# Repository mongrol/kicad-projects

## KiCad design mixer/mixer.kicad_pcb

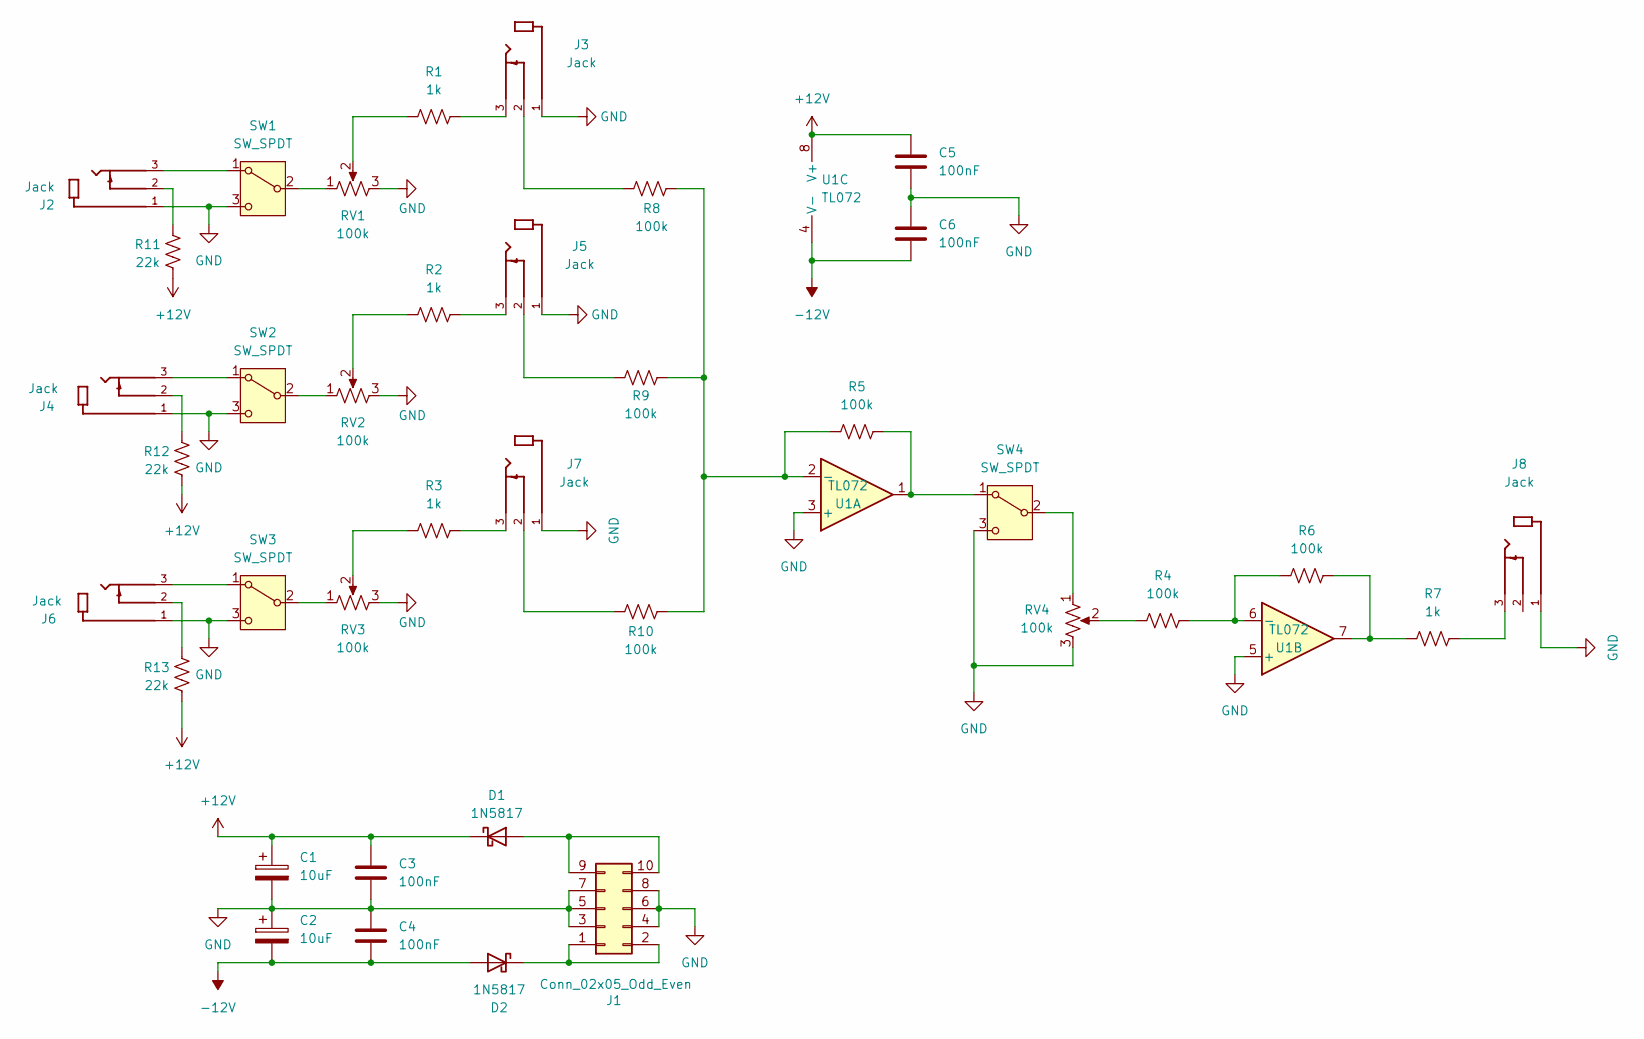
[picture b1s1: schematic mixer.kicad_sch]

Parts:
C1, C2: 10uF; CP_Elec_4x3
C3, C4, C5, C6: 100nF; C_0805_2012Metric_Pad1.18x1.45mm_HandSolder
D1, D2: 1N5817; D_SOD-323_HandSoldering
J1: Conn_02x05_Odd_Even; PinHeader_2x05_P2.54mm_Vertical
J2, J3, J4, J5, J6, J7, J8: Jack; Thonkiconn_J398SM_Vertical_CircularHoles; PARTREV 1
R1, R2, R3, R7: 1k; R_0805_2012Metric_Pad1.20x1.40mm_HandSolder
R4, R5, R6, R8, R9, R10: 100k; R_0805_2012Metric_Pad1.20x1.40mm_HandSolder
R11, R12, R13: 22k; R_0805_2012Metric_Pad1.20x1.40mm_HandSolder
RV1, RV2, RV3, RV4: 100k; Potentiometer_Bourns_PTA3043_Single_Slide
SW1, SW2, SW3, SW4: SW_SPDT; ToggleSwitch_MTS-102_SPDT
U1: TL072; SOIC-8_3.9x4.9mm_P1.27mm

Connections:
+12V: C1.1, C3.1, C5.1, D1.1 (K), R11.2, R12.2, R13.2, U1.8 (V+)
-12V: C2.2, C4.2, C6.2, D2.2 (A), U1.4 (V-)
GND: C1.2, C2.1, C3.2, C4.1, C5.2, C6.1, J1.3, J1.4, J1.5, J1.6, J1.7, J1.8, J2.1, J3.1, J4.1, J5.1, J6.1, J7.1, J8.1, RV1.3, RV2.3, RV3.3, RV4.3, SW1.3 (C), SW2.3 (C), SW3.3 (C), SW4.3 (C), U1.3 (+), U1.5 (+)
unnamed: D1.2 (A), J1.9, J1.10
unnamed: D2.1 (K), J1.1, J1.2
unnamed: J2.2, R11.1
unnamed: J3.2, R8.1
unnamed: J3.3, R1.2
unnamed: J4.2, R12.1
unnamed: J5.2, R9.1
unnamed: J5.3, R2.2
unnamed: J6.2, R13.1
unnamed: J7.2, R10.1
unnamed: J7.3, R3.2
unnamed: J8.3, R7.2
unnamed: R1.1, RV1.2
unnamed: R2.1, RV2.2
unnamed: R3.1, RV3.2
unnamed: R4.1, RV4.2
unnamed: R6.2, R7.1, U1.7
unnamed: J2.3, SW1.1 (A)
unnamed: RV1.1, SW1.2 (B)
unnamed: J4.3, SW2.1 (A)
unnamed: RV2.1, SW2.2 (B)
unnamed: J6.3, SW3.1 (A)
unnamed: RV3.1, SW3.2 (B)
unnamed: R5.2, SW4.1 (A), U1.1
unnamed: RV4.1, SW4.2 (B)
unnamed: R5.1, R8.2, R9.2, R10.2, U1.2 (-)
unnamed: R4.2, R6.1, U1.6 (-)

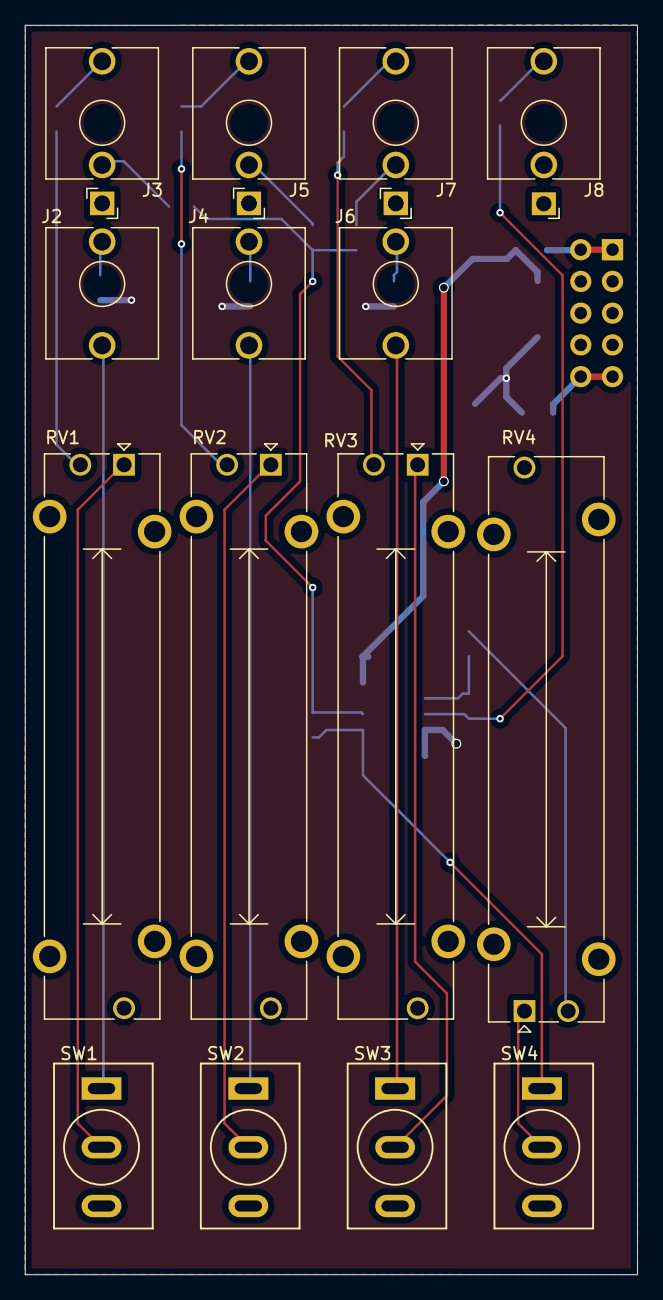
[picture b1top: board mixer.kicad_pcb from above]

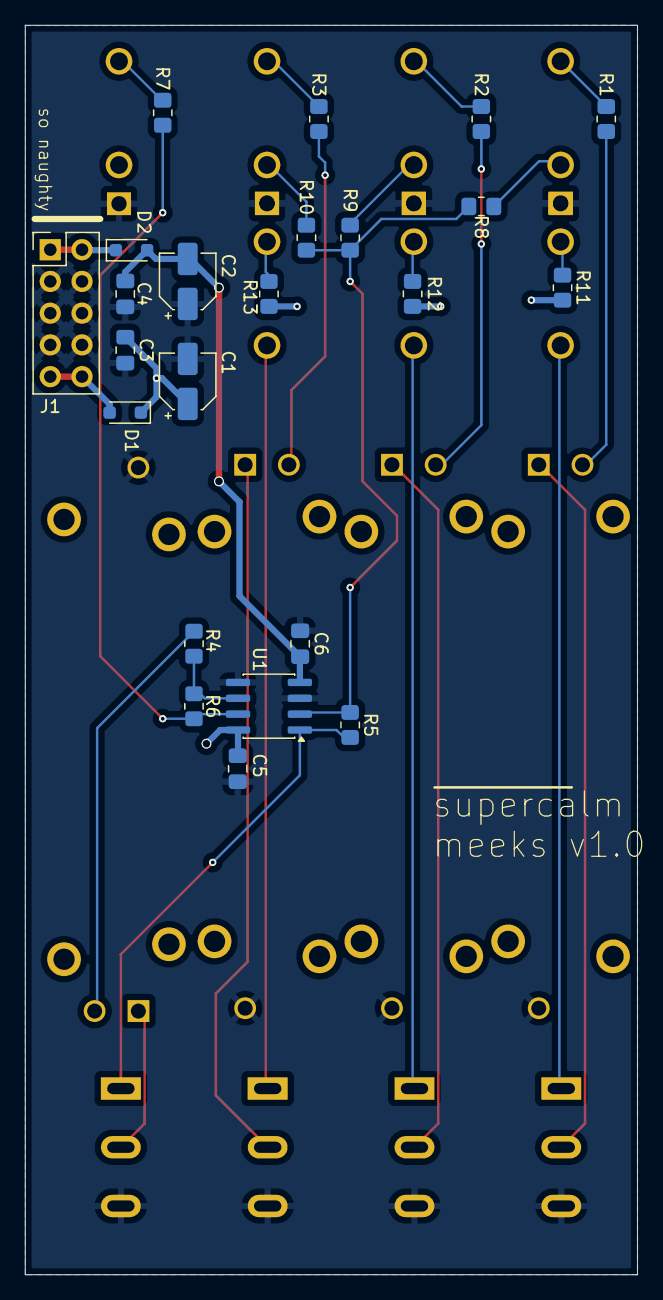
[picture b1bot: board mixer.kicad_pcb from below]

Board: 2 copper layers, 49.0 x 100.0 mm, 38 parts (23 on the bottom side), 30 nets.

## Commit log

2025-11-01 init
2025-11-09 sdsds
2025-11-14 fgdfg
2025-11-14 sdasd
